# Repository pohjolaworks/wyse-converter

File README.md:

# Wyse Converter

This project is merely a helper to make Wyse converter building more accessible. The person behind the firmware is [Soarer](https://geekhack.org/index.php?action=profile;u=4274), and is solely responsible for making this work. Thank you so much !

Meant to work with Soarer's Wyseverter, documented [in this GeekHack post](https://geekhack.org/index.php?topic=52597.0)

## Assembly
For assembling this converter:  
* 1x Converter pcb
* 1x Arduino Pro Micro clone (Mini OR Micro-usb, PCB supports both)
* 1x RJ9 PCB-mount connector such as [this one](https://www.aliexpress.com/item/1974919975.html?spm=a2g0s.9042311.0.0.3ab54c4dBx8Llu)
* 2x M3 mounting hardware (Screws and/or standoffs)

It is recommended to socket the Pro Micro controller by using [hotswap sockets](http://www.40percent.club/2018/03/sockets.html), there's plenty to choose from.

Solder the pro micro COMPONENTS AND USB PORT FACING DOWN on to the pcb, and then solder the 4P4C connector.

Flash the firmware using avrdude or QMK Toolbox and you're good to go !

## Case

Download the case from [Printables](https://www.printables.com/model/273160-wyse-converter-enclosure)

## Connector pinout

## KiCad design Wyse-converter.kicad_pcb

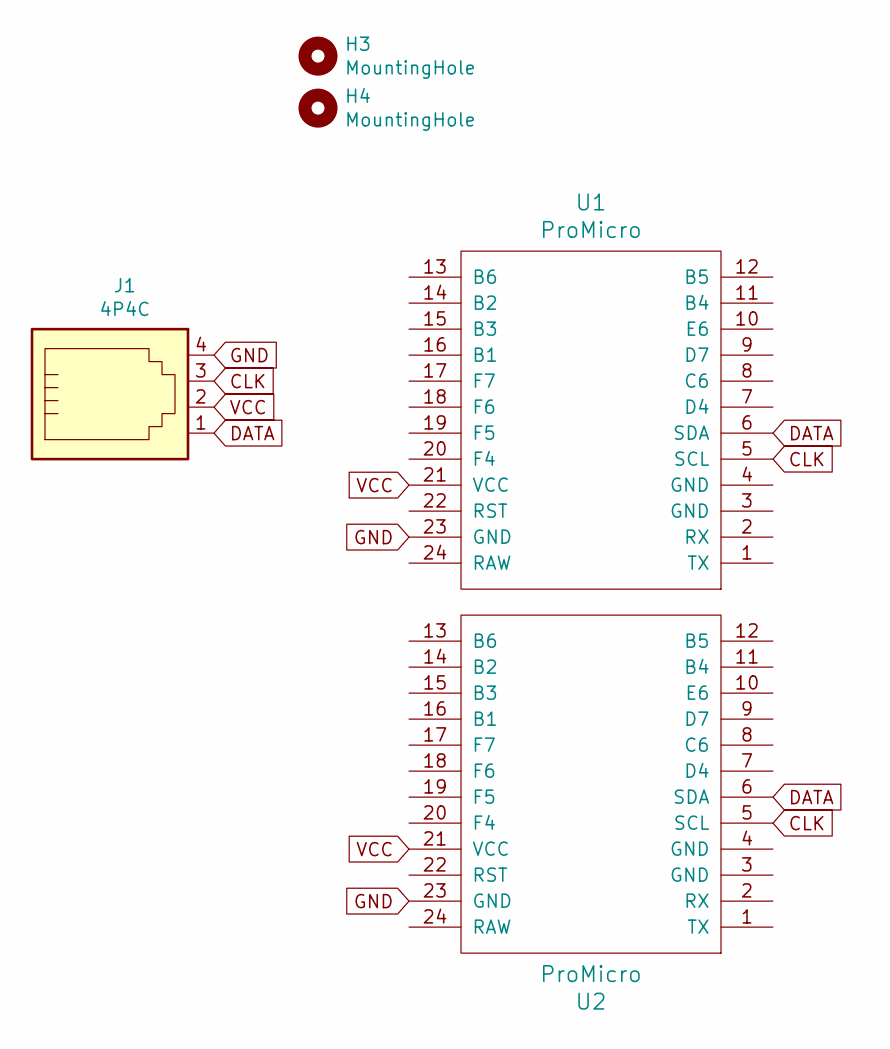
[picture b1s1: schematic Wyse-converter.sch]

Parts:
H3, H4: MountingHole; HOLE_M3
J1: 4P4C
U1: ProMicro; ArduinoProMicro
U2: ProMicro; ArduinoProMicro-Mini-USB-No-Text

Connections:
CLK: J1.3, U1.5 (SCL), U2.5 (SCL)
DATA: J1.1, U1.6 (SDA), U2.6 (SDA)
GND: J1.4, U1.23 (GND), U2.23 (GND)
VCC: J1.2, U1.21 (VCC), U2.21 (VCC)

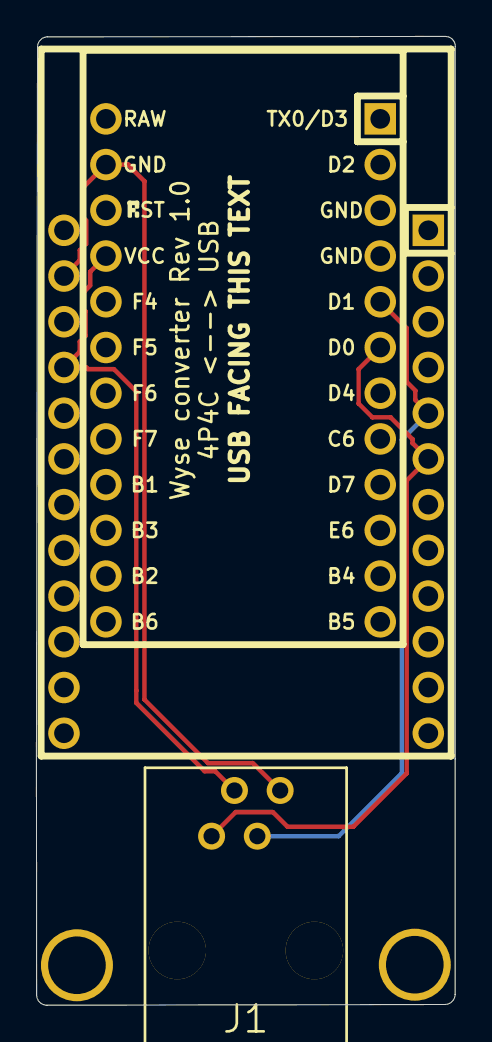
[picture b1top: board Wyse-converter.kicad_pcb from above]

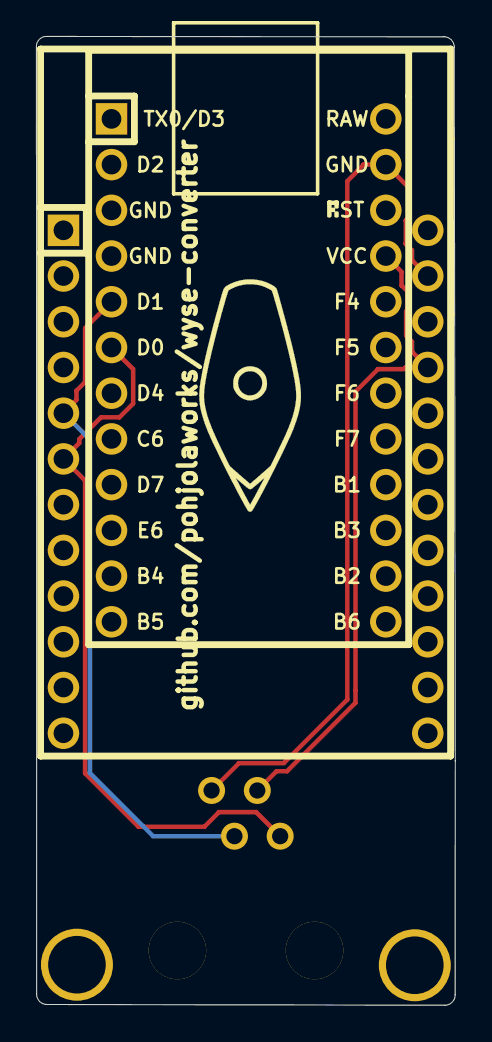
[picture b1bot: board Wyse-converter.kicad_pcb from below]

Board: 2 copper layers, 23.3 x 53.8 mm, 5 parts (2 on the bottom side), 4 nets.

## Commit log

2020-10-21 Add mounting hardware to assembly
2020-10-21 Add gerbers, improve docs
2021-06-25 Fixed and working version
2022-09-08 Add download link to enclosure
